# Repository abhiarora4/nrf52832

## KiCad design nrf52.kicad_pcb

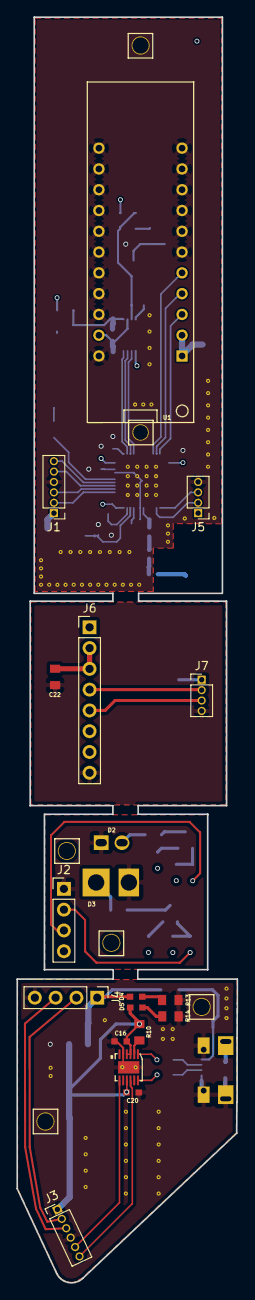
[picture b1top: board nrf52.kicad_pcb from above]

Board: 4 copper layers, 26.9 x 154.7 mm, 83 parts (0 on the bottom side), 59 nets.

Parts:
AE1: Antenna_Shield; chip_ant_2450AT18B100
C1, C2: 12pF; C_0402
C3: 0.8pF; C_0402
C4, C5, C8, C13, C16, C20, C27: 0.1uF; C_0603
C7: 100pF; C_0402
C9: 4.7uF; C_0603
C10, C24, C25: 1uF; C_0603
C11, C12, C18, C19, C22: 10uF; C_0805
C15: 10nF; C_0603
C17, C21: 47pF; C_0603
C23: C; C_0402
C26: 2.2nF; C_0603
C28, C29: 1nF; C_0603
D1: DEBUG_LED; LED_0805
D2: LED_1; led_428nm
D3: LED_2; led_22k
D4: RED_LED; LED_0603
D5: GREEN_LED; LED_0603
J1: CONN; Pin_Header_Straight_1x06_Pitch1.27mm
J2: CONN_USB; Pin_Header_Straight_1x04_Pitch2.54mm
J3: CONN_TCD; Pin_Header_Straight_1x06_Pitch1.27mm
J4: CONN_LED; Pin_Header_Straight_1x04_Pitch2.54mm
J5: CONN_PROG; Pin_Header_Straight_1x04_Pitch1.27mm
J6: CONN_DK; Pin_Header_Straight_1x08_Pitch2.54mm
J7: CONN_NRF52; Pin_Header_Straight_1x04_Pitch1.27mm
L1: 3.9nH; L_0402
L2: Ferrite_Bead; ferrite_bead_0603
L3, L4: L; L_0402
Q1, Q2: MMBT4401LT1G; bc860c_sot23
R1, R2, R3, R6, R7, R10: 1K; C_0805
R4: 150R; C_0805
R5, R9: SHORT; C_0805
R8, R11, R12: 27R; C_0805
R13, R14, R15: 470R; C_0805
R16, R17: 1K; R_0805
R18, R19: 10K; R_0805
TP1: TestPoint; TestPoint_4mm
TP2: TestPoint; TestPoint_2mm
U1: TCD1304; tcd1304ag
U2: nrf52832
U3: LM4041C; SOT_23_N
U4: MICRO-B_USB; USB_Micro-B_Molex
U5: FT234XD
U6: LM1117-3.3; lm1117
U7: ADS7042; VSSOP-8
U8: jumper_no; SolderBridge_NO
U9: AZ431L; SOT_23_N
Y1: 32MHz; crystal_2600M_32MHz
mh1, mh2, mh3, mh4, mh5, mh6: mh; mounting_hole

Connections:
/led_board/5V: D2.2, D3.2, J2.1
/led_board/LED_PWM_1: J2.3, R2.2
/led_board/LED_PWM_2: J2.2, R6.2
/nrf52_board/3V3: C5.1, C8.1, C9.1, C11.1, C12.1, C13.1, C24.1, C27.1, J1.1, J5.1, R1.2, R16.2, TP2.1, U1.1, U1.2, U2.13, U2.36, U2.48, U7.1
/nrf52_board/ANTENNA: C23.1, L1.1
/nrf52_board/AVDD/VREF+: C25.1, R16.1, R17.1, U7.7, U9.2
/nrf52_board/DEBUG_PIN: R15.2, U2.43
/nrf52_board/LED_PWM_1: J1.3, U2.40
/nrf52_board/LED_PWM_2: J1.2, U2.39
/nrf52_board/NRF_SWCLK: J5.3, U2.25
/nrf52_board/NRF_SWDO: J5.2, U2.26
/nrf52_board/RX: J1.6, U2.42
/nrf52_board/SCLK: U2.4, U7.2
/nrf52_board/SDO: U2.3, U7.3
/nrf52_board/TCD_ICG: U1.3, U2.12
/nrf52_board/TCD_MCLK: U1.4, U2.11
/nrf52_board/TCD_OS: C26.1, C29.1, U1.21, U7.6
/nrf52_board/TCD_SHFT: U1.5, U2.10
/nrf52_board/TX: J1.5, U2.41
/nrf52_board/VREF-: C26.2, C28.2, R1.1, U3.1, U7.5
/nrf52_board/~CS: U2.2, U7.4
/program/3V3: C22.1, J6.2, J6.3, U8.2
/program/SCLK: J6.5, J7.3
/program/SDO: J6.4, J7.2
/usb_board/3V3: C16.2, C19.1, C20.2, D5.2, J3.1, R10.1, U5.3, U5.4, U5.9, U6.2, U6.4
/usb_board/LED_PWM_1: J3.3, J4.3
/usb_board/LED_PWM_2: J3.2, J4.2
/usb_board/RX_UART: J3.5, U5.7
/usb_board/TX_UART: J3.6, U5.10
/usb_board/USB_5V: C18.1, D4.2, J4.1, L2.1, U6.3
/usb_board/USB_D+: C21.1, R12.2, U4.3
/usb_board/USB_D-: C17.1, R11.2, U4.2
GND: C1.2, C2.2, C3.2, C4.2, C5.2, C7.2, C8.2, C9.2, C10.2, C11.2, C12.2, C13.2, C15.2, C16.1, C17.2, C18.2, C19.2, C20.1, C21.2, C22.2, C24.2, C25.2, C27.2, C28.1, C29.2, D1.1, J1.4, J2.4, J3.4, J4.4, J5.4, J6.8, J7.4, L3.1, R3.1, R5.2, R7.1, R9.2, R13.1, R14.1, R19.2, TP1.1, U1.6, U1.7, U1.8, U1.9, U1.10, U1.11, U1.12, U1.13, U1.14, U1.15, U1.16, U1.17, U1.18, U1.19, U1.20, U1.22, U2.31, U2.45, U3.2, U3.3, U4.4, U4.5, U5.5, U6.1, U7.8, U9.3, Y1.2, Y1.4, mh1.1, mh2.1, mh3.1, mh4.1, mh5.1, mh6.1
unnamed: AE1.1, L4.2
unnamed: C1.1, U2.34, Y1.3
unnamed: C2.1, U2.35, Y1.1
unnamed: C3.1, L1.2, U2.30
unnamed: C4.1, U2.1
unnamed: C7.1, U2.33
unnamed: C10.1, U2.46
unnamed: C15.1, L2.2, U4.1
unnamed: C23.2, L3.2, L4.1
unnamed: D1.2, R15.1
unnamed: D2.1, R4.1
unnamed: D3.1, R8.1
unnamed: D4.1, R13.2
unnamed: D5.1, R14.2
unnamed: J7.1, U8.1
unnamed: Q1.1, R2.1, R3.2
unnamed: Q1.2, R5.1
unnamed: Q1.3, R4.2
unnamed: Q2.1, R6.1, R7.2
unnamed: Q2.2, R9.1
unnamed: Q2.3, R8.2
unnamed: R10.2, U5.2
unnamed: R11.1, U5.1
unnamed: R12.1, U5.12
unnamed: R17.2, R18.1
unnamed: R18.2, R19.1, U9.1
